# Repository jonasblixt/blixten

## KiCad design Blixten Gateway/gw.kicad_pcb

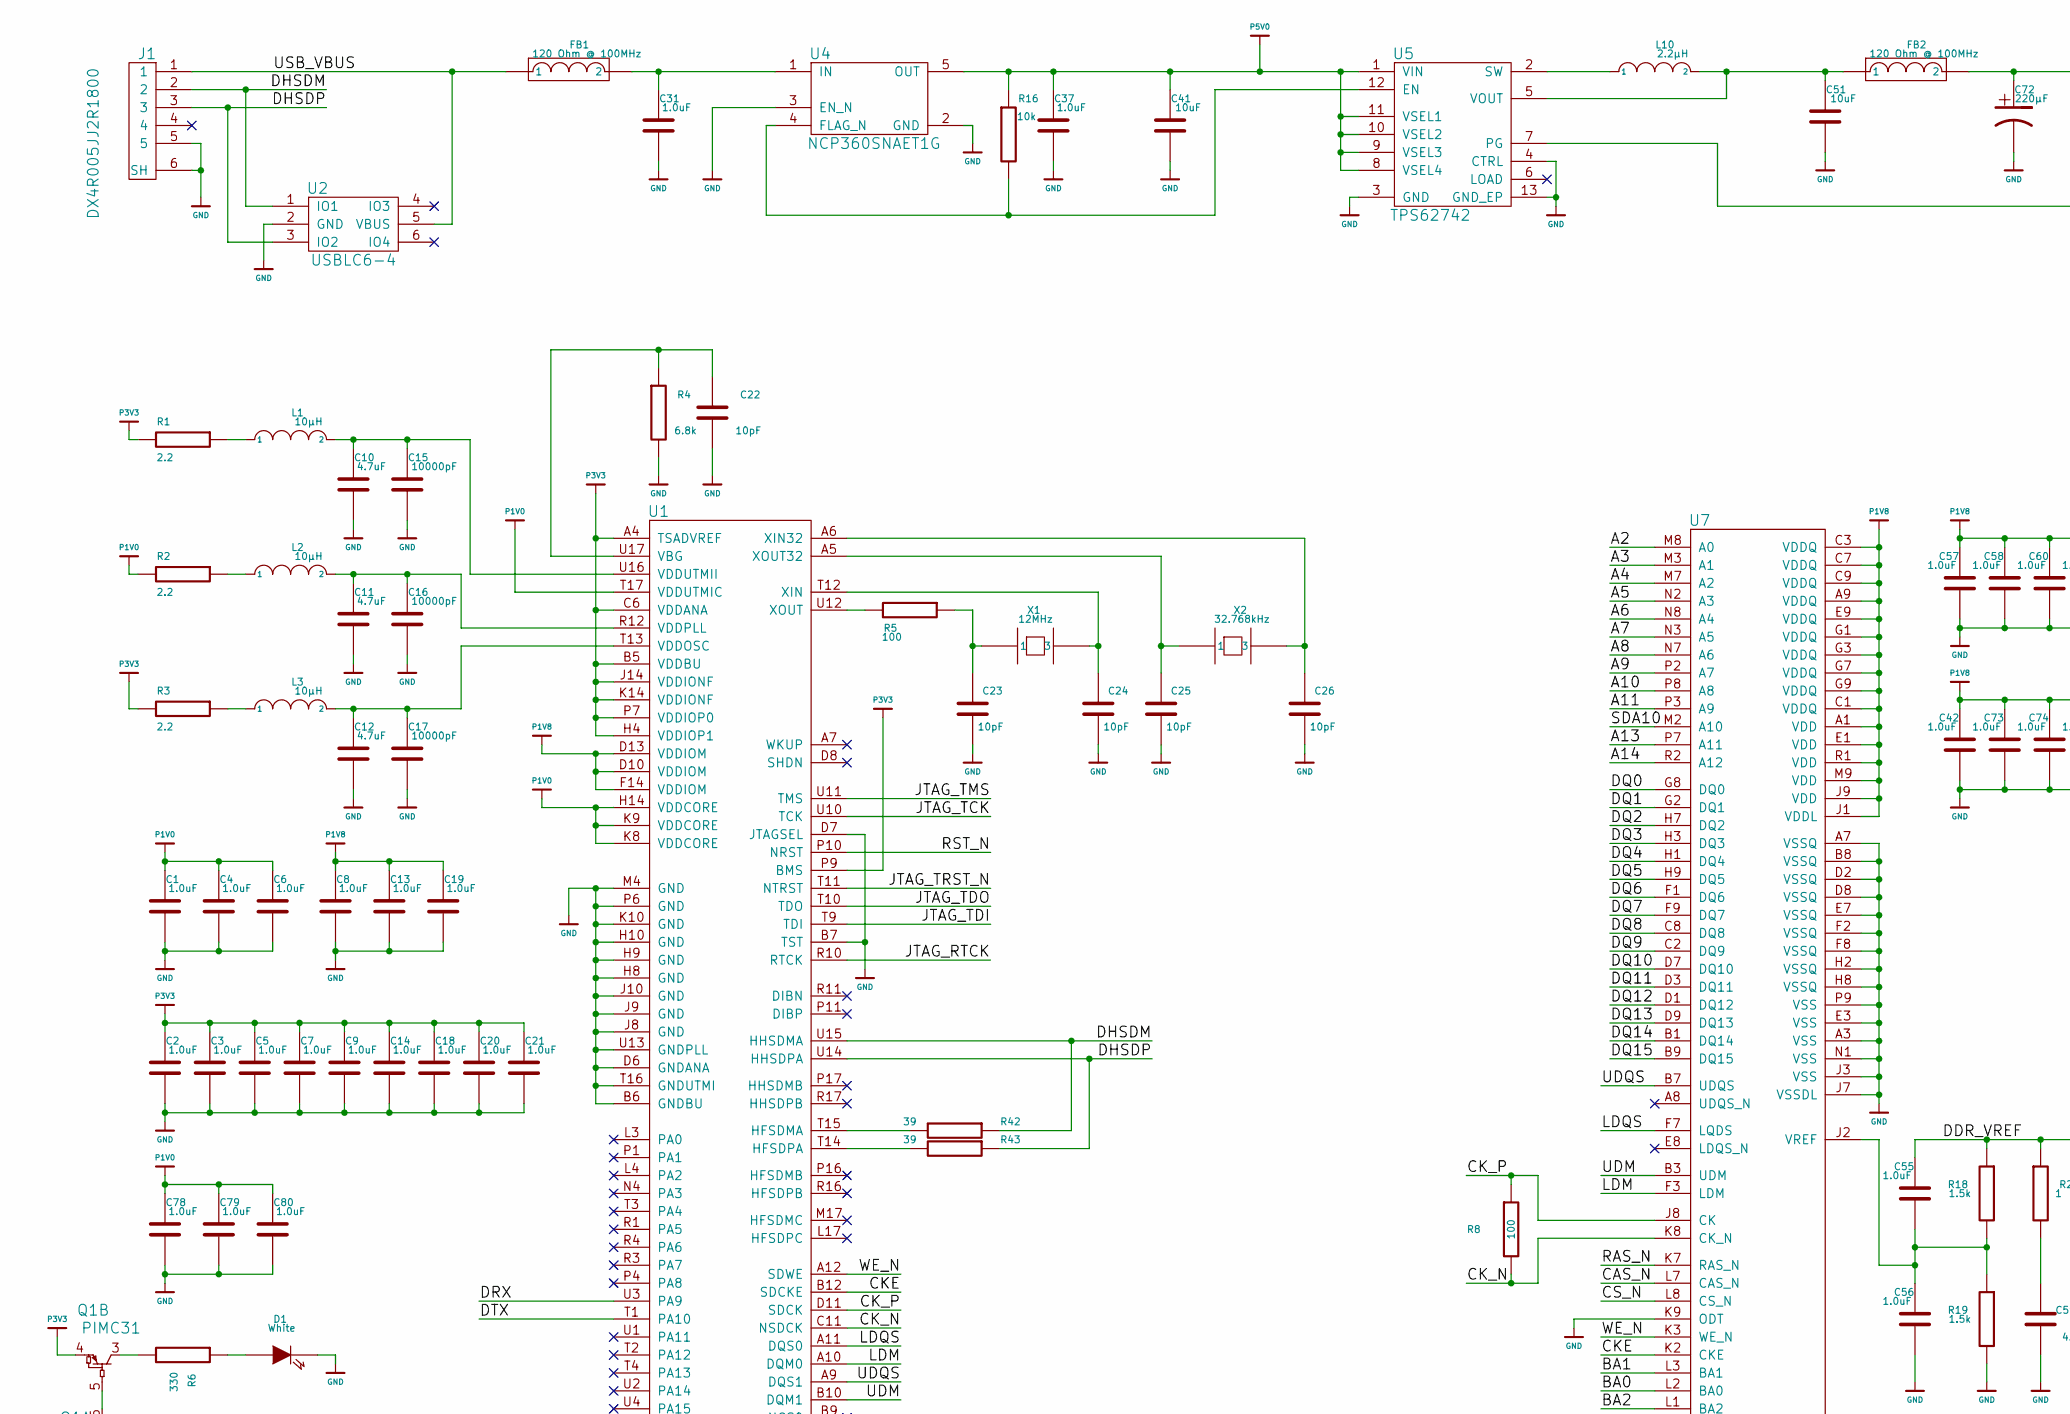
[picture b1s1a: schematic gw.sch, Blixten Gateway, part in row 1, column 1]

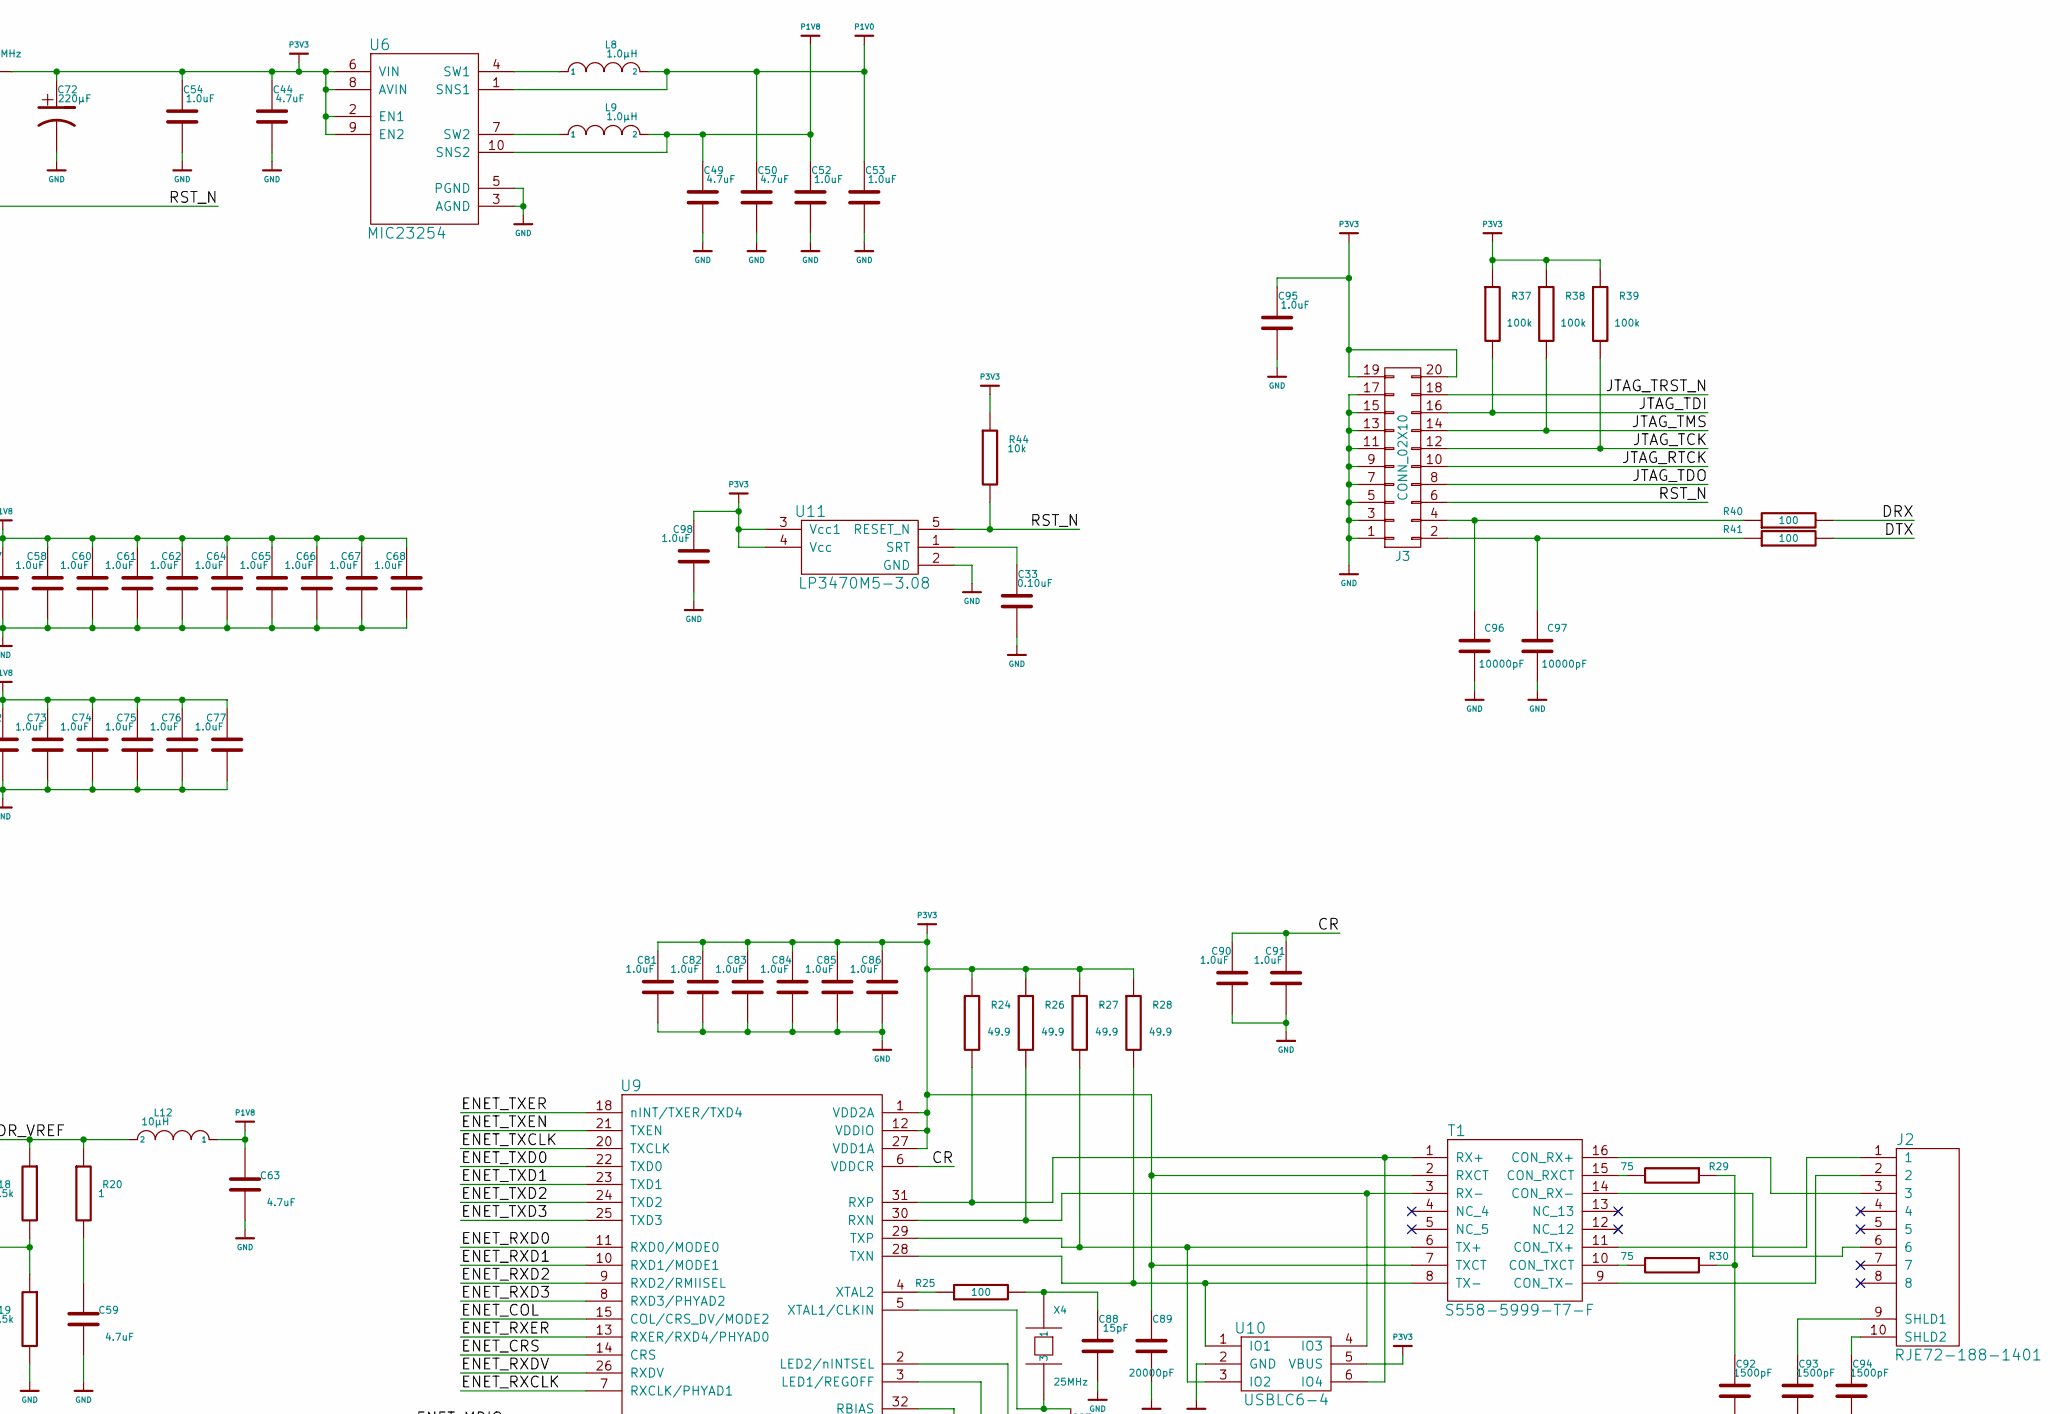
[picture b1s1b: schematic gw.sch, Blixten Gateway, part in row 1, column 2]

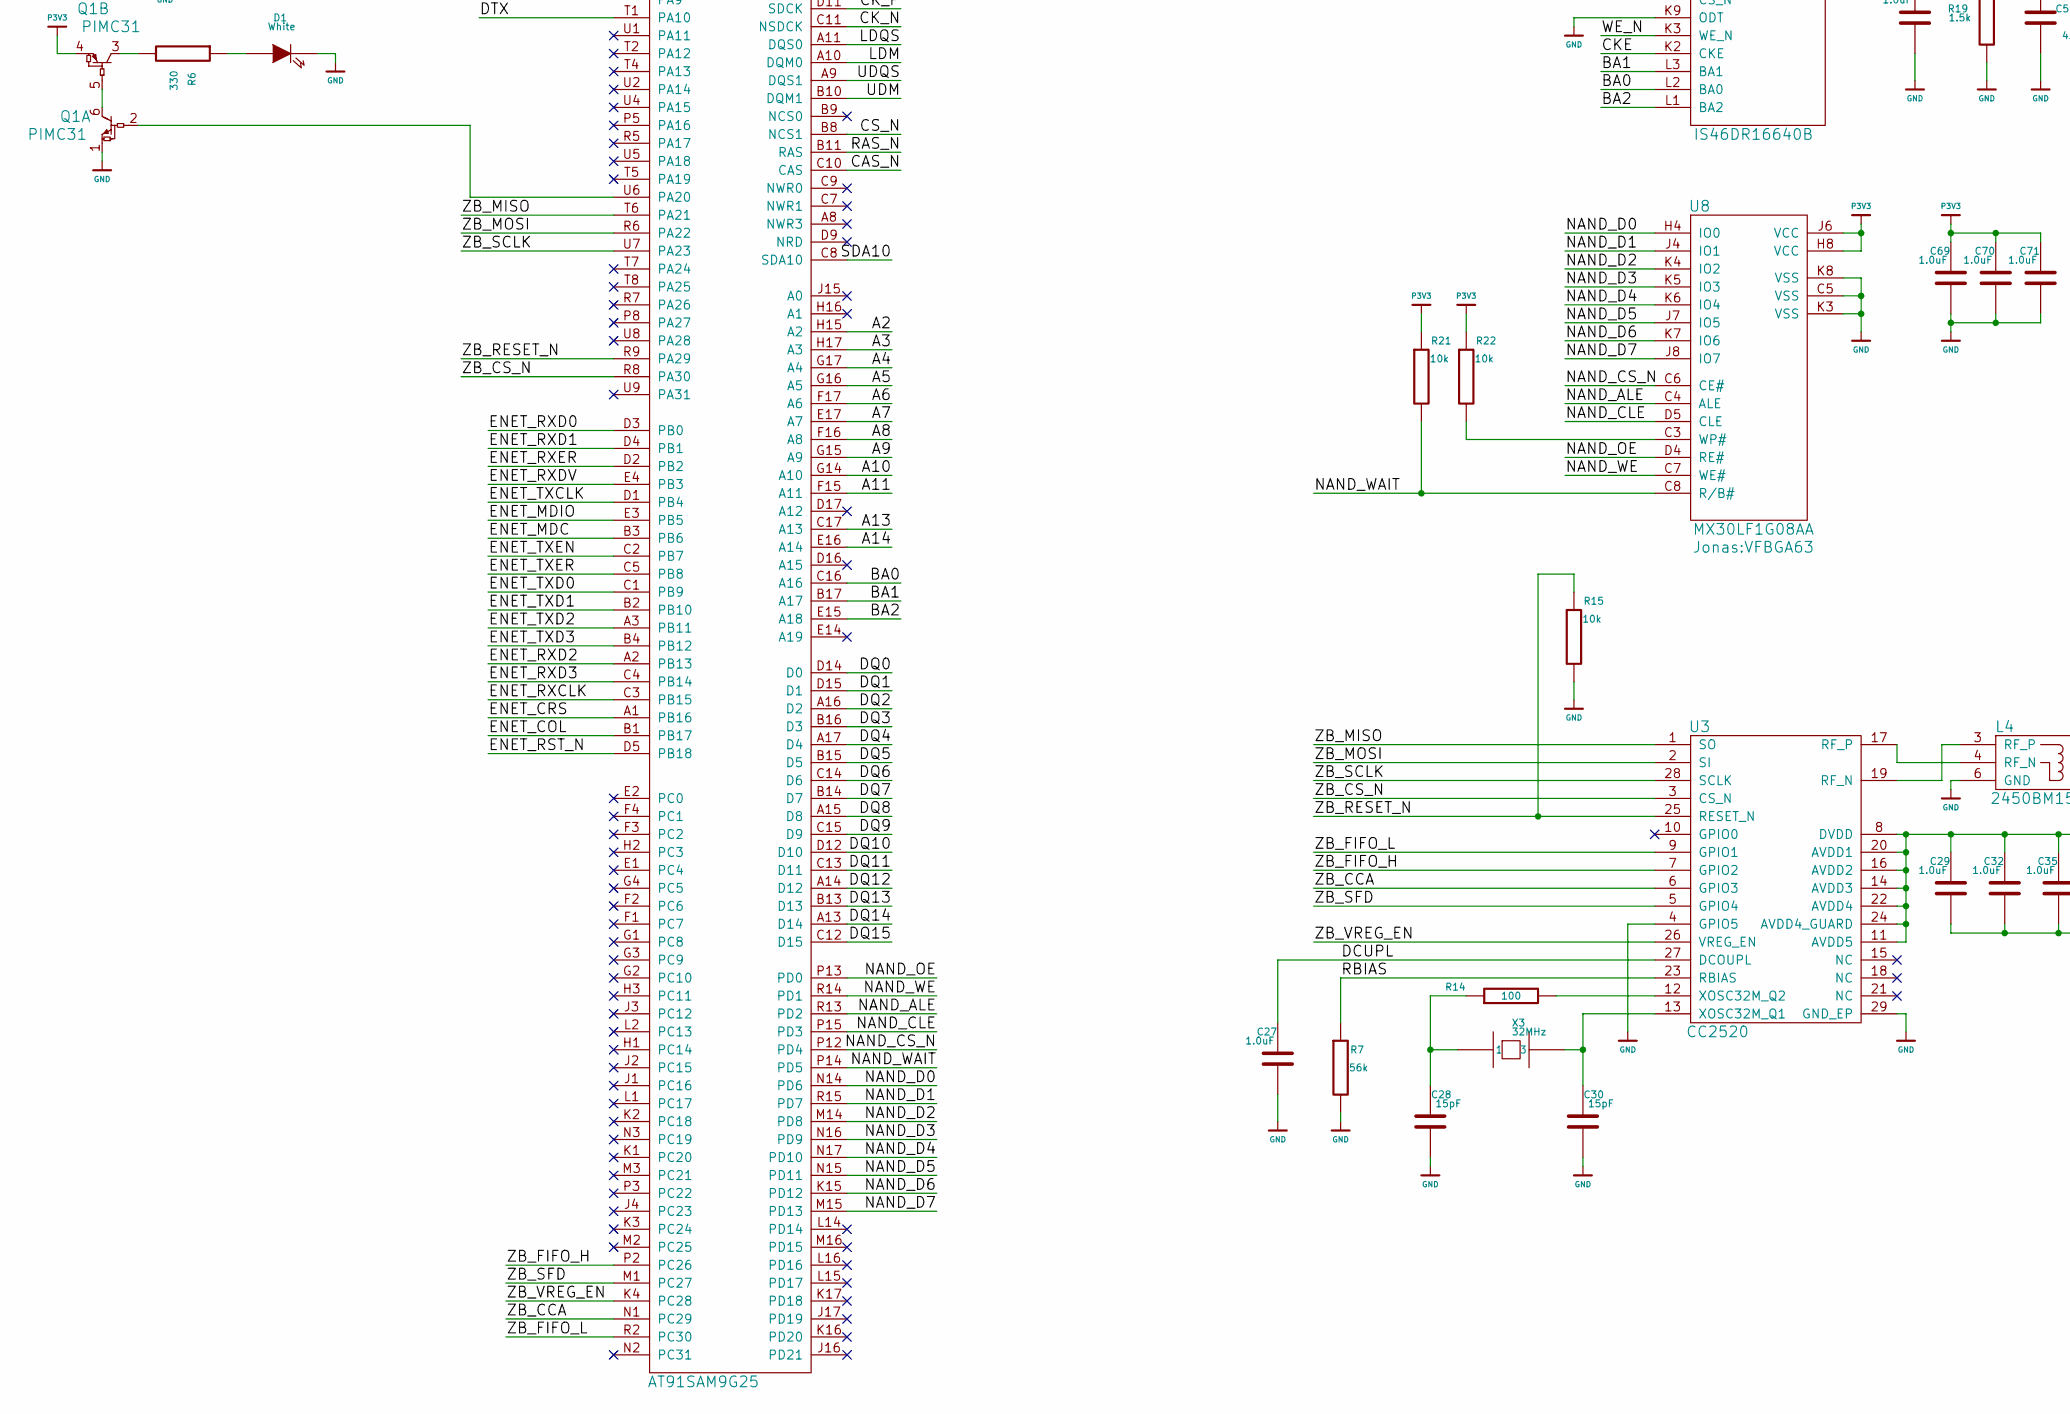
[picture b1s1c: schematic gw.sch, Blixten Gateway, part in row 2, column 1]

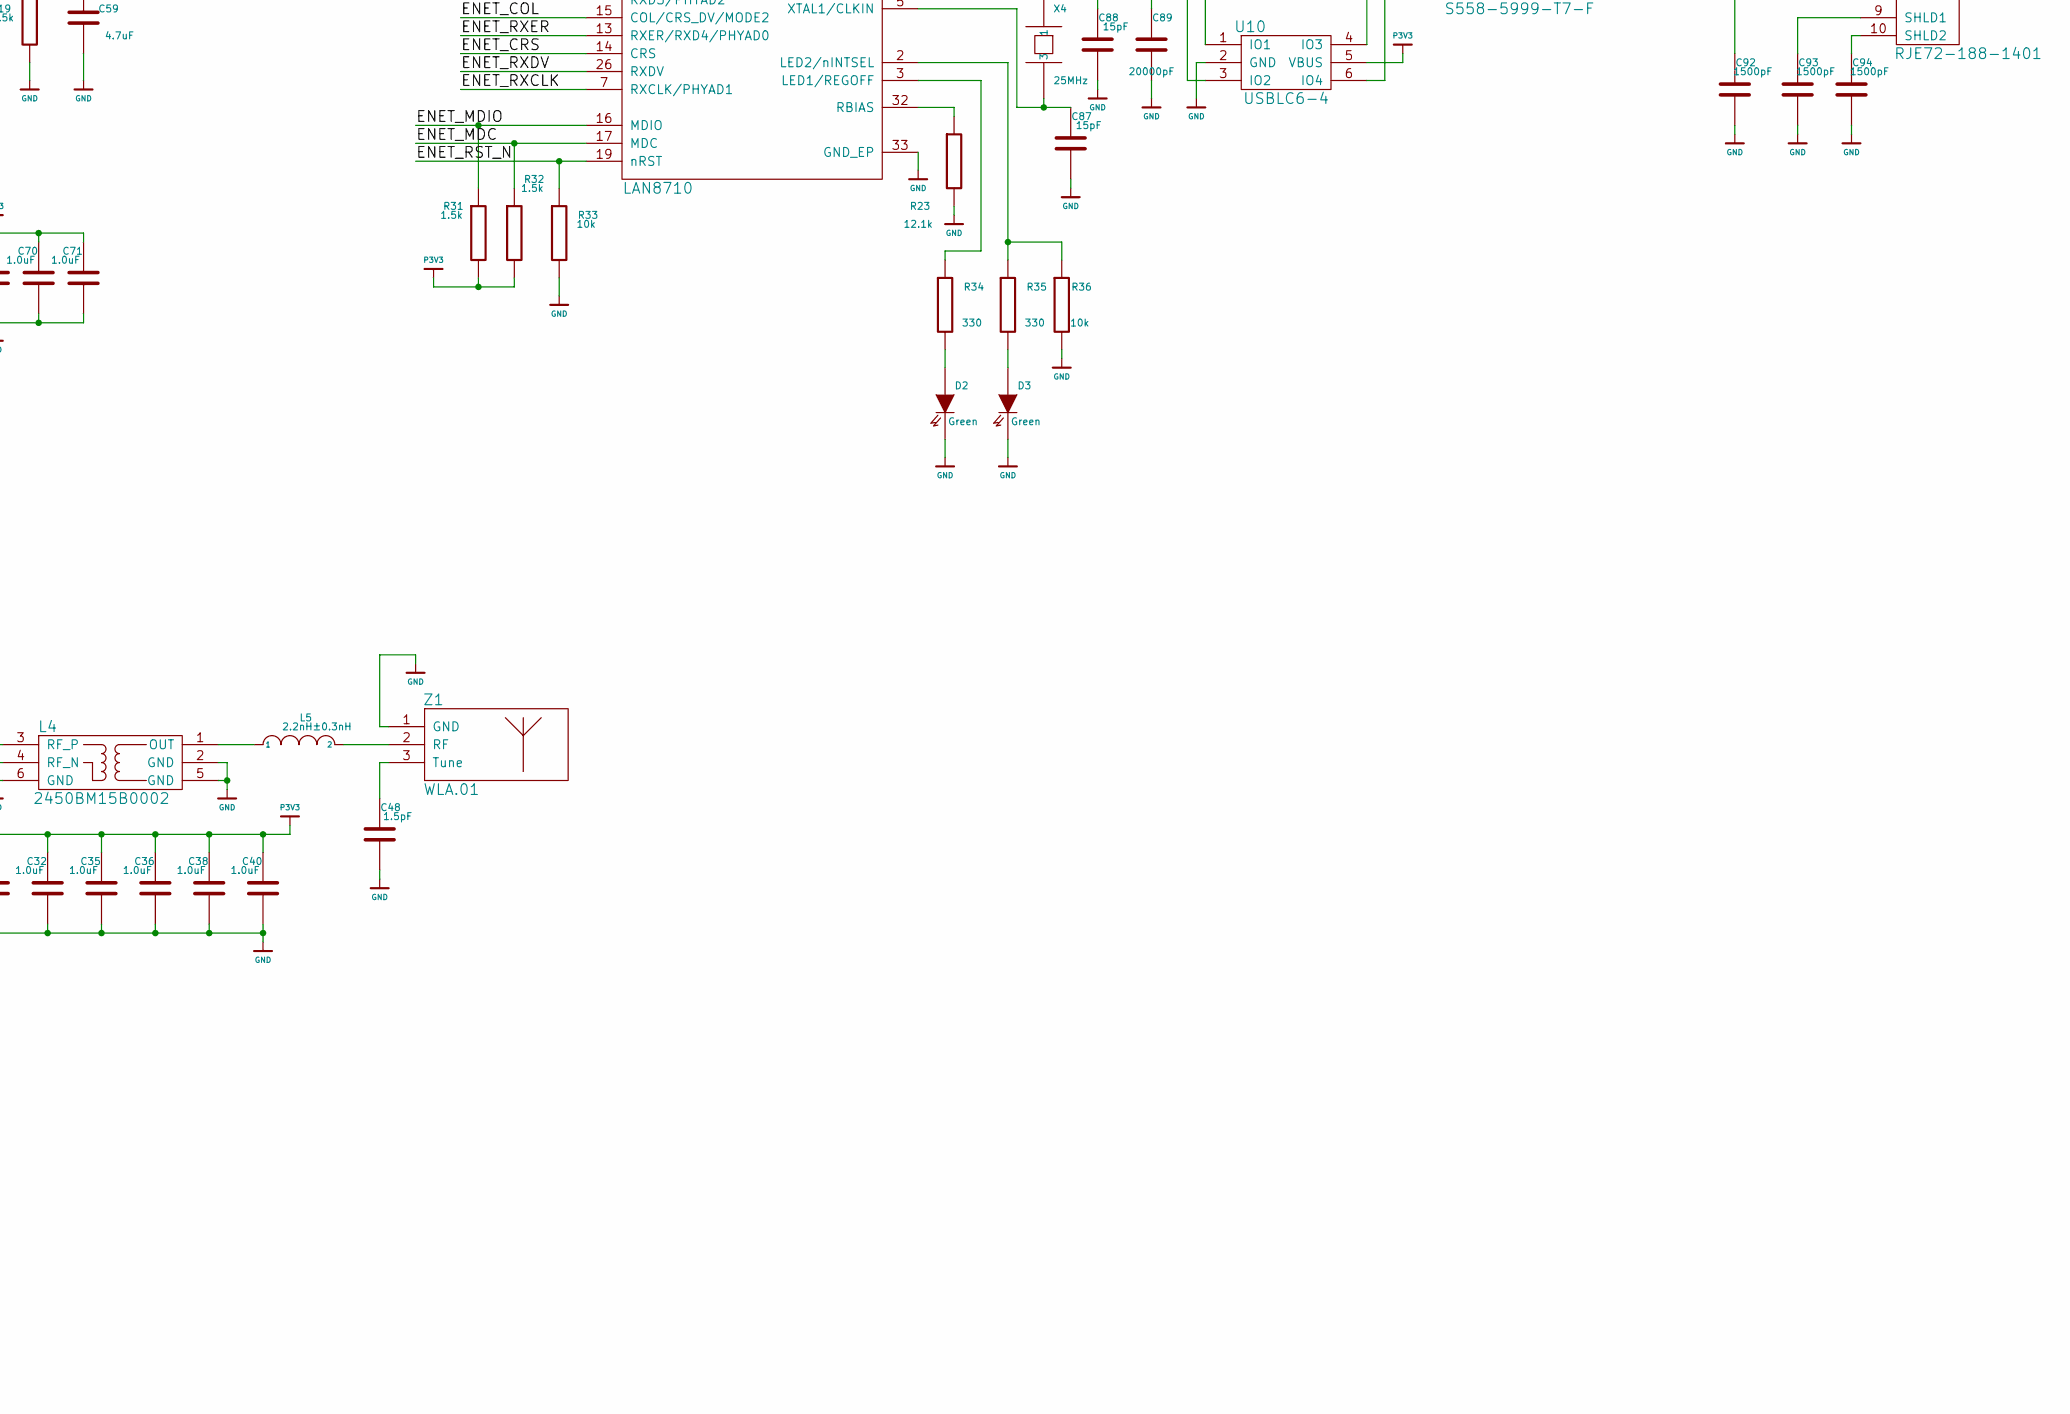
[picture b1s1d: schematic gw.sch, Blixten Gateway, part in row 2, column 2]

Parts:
C1, C2, C3, C4, C5, C6, C7, C8, C9, C13, C14, C18, C19, C20, C21, C27, C29, C32, C35, C36, C38, C40, C42, C52, C53, C55, C56, C57, C58, C60, C61, C62, C64, C65, C66, C67, C68, C69, C70, C71, C73, C74, C75, C76, C77, C78, C79, C80, C81, C82, C83, C84, C85, C86, C90, C91, C95, C98: C0402_1u_10Vdc_X5R; C_0402; Part Number GRM153R61A105ME95
C10, C11, C12, C44, C49, C50, C59, C63: C0603_4u7_6.3Vdc_X5R; C_0603; Part Number GRM185R60J475ME15
C15, C16, C17: C0402_10n_10Vdc_X5R; C_0402; Part Number GRM155R61A103KA01
C22, C23, C24, C25, C26: C0402_10p_100Vdc_C0G; C_0402; Part Number GRM1555C2A100GA01
C28, C30, C87, C88: C0402_15p_100Vdc_C0G; C_0402; Part Number GRM1555C2A150GA01
C31, C37, C54: C0603_1u_25Vdc_X7R; C_0603; Part Number GRM188R71E105KA12
C33: C0402_100n_100Vdc_X5R; C_0402; Part Number GRM155R62A104KE14
C41, C51: C0805_10u_25Vdc_X7R; C_0805; Part Number GRM21BZ71E106KE15
C48: C0402_1p5_100Vdc_C0G; C_0402; Part Number GRM1555C2A1R5BA01
C72: PCAP_220u_11; c_elec_5x5.3; Part Number PCG0G221MCO1GS
C89: C0805_20n_50Vdc_X7R; C_0805; Part Number GRM21BR71H203JA01
C92, C93, C94: C1206_1n5_1000Vdc_X7R; C_1206; Part Number GRM31BR73A152KW01
C96, C97: C0402_10n_50Vdc_X7R; C_0402; Part Number GRM155R71H103KA88
D1: LED0402_SMLP13WBC8W1; LED_0603; Part Number SMLP13WBC8W1
D2, D3: LED0402_SML-P11MTT86; LED_0603; Part Number SML-P11MTT86
FB1, FB2: BL0603_BLM18KG121TN1D; R_0603; Part Number BLM18KG121TN1D
J1: DX4R005JJ2R1800; USB_Micro-B
J2: RJE72-188-1401
J3: CONN_02X10; TFM-110-02-S-D-WT
L1, L2, L3: LQM21FN100N00L; R_0805; Part Number LQM21FN100N00L
L4: 2450BM15B0002
L5: LQG15HN_2n2; R_0402; Part Number LQG15HN2N2S02p
L8, L9: LQM21PN1R0MC0D; R_0805; Part Number LQM21PN1R0MC0D
L10: IHLP1212_2u2_2; IHLP1212; Part Number IHLP1212BZER2R2M11
L12: LQH2MCN100K02L; R_0805; Part Number LQH2MCN100K02L
Q1: PIMC31; SOT-23-6
R1, R2, R3: R0402_2R20; R_0402; Part Number CRCW04022R20FKED
R4: R0402_6k80; R_0402; Part Number CRCW04026K80FKED
R5, R8, R14, R25, R40, R41: R0402_100R; R_0402; Part Number CRCW0402100RFKED
R6, R34, R35: R0402_330R; R_0402; Part Number CRCW0402330RFKED
R7: R0402_56k; R_0402; Part Number CRCW040256K0FKED
R15, R16, R21, R22, R33, R36, R44: R0402_10k; R_0402; Part Number CRCW040210K0FKED
R18, R19, R31, R32: R0402_1k50; R_0402; Part Number CRCW04021K50FKED
R20: R0402_1R; R_0402; Part Number CRCW04021R00FKED
R23: R0402_12k10; R_0402; Part Number CRCW040212K1FKED
R24, R26, R27, R28: R0603_49R90; R_0603; Part Number CRCW060349R9FKEA
R29, R30: R0603_75R; R_0603; Part Number CRCW060375R0FKEA
R37, R38, R39: R0402_100k; R_0402; Part Number CRCW0402100KFKED
R42, R43: R0402_39R; R_0402; Part Number CRCW040239R0FKED
T1: S558-5999-T7-F; SO-16-W
U1: AT91SAM9G25; 217LFBGA
U2, U10: USBLC6-4; SOT-23-6
U3: CC2520; QFN-28-1EP_5x5mm_Pitch0.5mm
U4: NCP360SNAET1G; SOT-23-5
U5: TPS62742; R-PWSON-N12
U6: MIC23254; MLF-10
U7: IS46DR16640B; BGA-90-0.8mm
U8: MX30LF1G08AA; VFBGA63
U9: LAN8710; QFN-32-1EP_5x5mm_Pitch0.5mm
U11: LP3470M5-3.08; SOT-23-5
X1: NX3225GA-12.000M-STD-CRA-1; NX3225; Part Number NX3225GA-12.000M-STD-CRA-1
X2: NX2012SA-32.768K-STD-MUB-1; NX2012; Part Number NX2012SA-32.768K-STD-MUB-1
X3: NX2520SA-32.000000MHZ; NX2520; Part Number NX2520SA-32.000000MHZ
X4: NX2520SA-25.000M-STD-CSW-5; NX2520; Part Number NX2520SA-25.000M-STD-CSW-5
Z1: WLA.01

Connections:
/A2: U1.H15 (A2), U7.M8 (A0)
/A3: U1.H17 (A3), U7.M3 (A1)
/A4: U1.G17 (A4), U7.M7 (A2)
/A5: U1.G16 (A5), U7.N2 (A3)
/A6: U1.F17 (A6), U7.N8 (A4)
/A7: U1.E17 (A7), U7.N3 (A5)
/A8: U1.F16 (A8), U7.N7 (A6)
/A9: U1.G15 (A9), U7.P2 (A7)
/A10: U1.G14 (A10), U7.P8 (A8)
/A11: U1.F15 (A11), U7.P3 (A9)
/A13: U1.C17 (A13), U7.P7 (A11)
/A14: U1.E16 (A14), U7.R2 (A12)
/BA0: U1.C16 (A16), U7.L2 (BA0)
/BA1: U1.B17 (A17), U7.L3 (BA1)
/BA2: U1.E15 (A18), U7.L1 (BA2)
/CAS_N: U1.C10 (CAS), U7.L7 (CAS_N)
/CKE: U1.B12 (SDCKE), U7.K2 (CKE)
/CK_N: R8.2, U1.C11 (NSDCK), U7.K8 (CK_N)
/CK_P: R8.1, U1.D11 (SDCK), U7.J8 (CK)
/CR: C90.1, C91.1, U9.6 (VDDCR)
/CS_N: U1.B8 (NCS1), U7.L8 (CS_N)
/DCUPL: C27.1, U3.27 (DCOUPL)
/DDR_VREF: C55.1, L12.2, R18.1, R20.1
/DHSDM: J1.2, R42.1, U1.U15 (HHSDMA), U2.1 (IO1)
/DHSDP: J1.3, R43.1, U1.U14 (HHSDPA), U2.3 (IO2)
/DQ0: U1.D14 (D0), U7.G8 (DQ0)
/DQ1: U1.D15 (D1), U7.G2 (DQ1)
/DQ2: U1.A16 (D2), U7.H7 (DQ2)
/DQ3: U1.B16 (D3), U7.H3 (DQ3)
/DQ4: U1.A17 (D4), U7.H1 (DQ4)
/DQ5: U1.B15 (D5), U7.H9 (DQ5)
/DQ6: U1.C14 (D6), U7.F1 (DQ6)
/DQ7: U1.B14 (D7), U7.F9 (DQ7)
/DQ8: U1.A15 (D8), U7.C8 (DQ8)
/DQ9: U1.C15 (D9), U7.C2 (DQ9)
/DQ10: U1.D12 (D10), U7.D7 (DQ10)
/DQ11: U1.C13 (D11), U7.D3 (DQ11)
/DQ12: U1.A14 (D12), U7.D1 (DQ12)
/DQ13: U1.B13 (D13), U7.D9 (DQ13)
/DQ14: U1.A13 (D14), U7.B1 (DQ14)
/DQ15: U1.C12 (D15), U7.B9 (DQ15)
/DRX: R40.2, U1.U3 (PA9)
/DTX: R41.2, U1.T1 (PA10)
/ENET_COL: U1.B1 (PB17), U9.15 (COL/CRS_DV/MODE2)
/ENET_CRS: U1.A1 (PB16), U9.14 (CRS)
/ENET_MDC: R32.1, U1.B3 (PB6), U9.17 (MDC)
/ENET_MDIO: R31.1, U1.E3 (PB5), U9.16 (MDIO)
/ENET_RST_N: R33.1, U1.D5 (PB18), U9.19 (nRST)
/ENET_RXCLK: U1.C3 (PB15), U9.7 (RXCLK/PHYAD1)
/ENET_RXD0: U1.D3 (PB0), U9.11 (RXD0/MODE0)
/ENET_RXD1: U1.D4 (PB1), U9.10 (RXD1/MODE1)
/ENET_RXD2: U1.A2 (PB13), U9.9 (RXD2/RMIISEL)
/ENET_RXD3: U1.C4 (PB14), U9.8 (RXD3/PHYAD2)
/ENET_RXDV: U1.E4 (PB3), U9.26 (RXDV)
/ENET_RXER: U1.D2 (PB2), U9.13 (RXER/RXD4/PHYAD0)
/ENET_TXCLK: U1.D1 (PB4), U9.20 (TXCLK)
/ENET_TXD0: U1.C1 (PB9), U9.22 (TXD0)
/ENET_TXD1: U1.B2 (PB10), U9.23 (TXD1)
/ENET_TXD2: U1.A3 (PB11), U9.24 (TXD2)
/ENET_TXD3: U1.B4 (PB12), U9.25 (TXD3)
/ENET_TXEN: U1.C2 (PB7), U9.21 (TXEN)
/ENET_TXER: U1.C5 (PB8), U9.18 (nINT/TXER/TXD4)
/JTAG_RTCK: J3.10, U1.R10 (RTCK)
/JTAG_TCK: J3.12, R39.2, U1.U10 (TCK)
/JTAG_TDI: J3.16, R37.2, U1.T9 (TDI)
/JTAG_TDO: J3.8, U1.T10 (TDO)
/JTAG_TMS: J3.14, R38.2, U1.U11 (TMS)
/JTAG_TRST_N: J3.18, U1.T11 (NTRST)
/LDM: U1.A10 (DQM0), U7.F3 (LDM)
/LDQS: U1.A11 (DQS0), U7.F7 (LQDS)
/NAND_ALE: U1.R13 (PD2), U8.C4 (ALE)
/NAND_CLE: U1.P15 (PD3), U8.D5 (CLE)
/NAND_CS_N: U1.P12 (PD4), U8.C6 (CE#)
/NAND_D0: U1.N14 (PD6), U8.H4 (IO0)
/NAND_D1: U1.R15 (PD7), U8.J4 (IO1)
/NAND_D2: U1.M14 (PD8), U8.K4 (IO2)
/NAND_D3: U1.N16 (PD9), U8.K5 (IO3)
/NAND_D4: U1.N17 (PD10), U8.K6 (IO4)
/NAND_D5: U1.N15 (PD11), U8.J7 (IO5)
/NAND_D6: U1.K15 (PD12), U8.K7 (IO6)
/NAND_D7: U1.M15 (PD13), U8.J8 (IO7)
/NAND_OE: U1.P13 (PD0), U8.D4 (RE#)
/NAND_WAIT: R21.2, U1.P14 (PD5), U8.C8 (R/B#)
/NAND_WE: U1.R14 (PD1), U8.C7 (WE#)
/RAS_N: U1.B11 (RAS), U7.K7 (RAS_N)
/RBIAS: R7.1, U3.23 (RBIAS)
/RST_N: J3.6, R44.2, U1.P10 (NRST), U5.7 (PG), U11.5 (RESET_N)
/SDA10: U1.C8 (SDA10), U7.M2 (A10)
/UDM: U1.B10 (DQM1), U7.B3 (UDM)
/UDQS: U1.A9 (DQS1), U7.B7 (UDQS)
/USB_VBUS: FB1.1, J1.1, U2.5 (VBUS)
/WE_N: U1.A12 (SDWE), U7.K3 (WE_N)
/ZB_CCA: U1.N1 (PC29), U3.6 (GPIO3)
/ZB_CS_N: U1.R8 (PA30), U3.3 (CS_N)
/ZB_FIFO_H: U1.P2 (PC26), U3.7 (GPIO2)
/ZB_FIFO_L: U1.R2 (PC30), U3.9 (GPIO1)
/ZB_MISO: U1.T6 (PA21), U3.1 (SO)
/ZB_MOSI: U1.R6 (PA22), U3.2 (SI)
/ZB_RESET_N: R15.1, U1.R9 (PA29), U3.25 (RESET_N)
/ZB_SCLK: U1.U7 (PA23), U3.28 (SCLK)
/ZB_SFD: U1.M1 (PC27), U3.5 (GPIO4)
/ZB_VREG_EN: U1.K4 (PC28), U3.26 (VREG_EN)
GND: C1.2, C2.2, C3.2, C4.2, C5.2, C6.2, C7.2, C8.2, C9.2, C10.2, C11.2, C12.2, C13.2, C14.2, C15.2, C16.2, C17.2, C18.2, C19.2, C20.2, C21.2, C22.2, C23.2, C24.2, C25.2, C26.2, C27.2, C28.2, C29.2, C30.2, C31.2, C32.2, C33.2, C35.2, C36.2, C37.2, C38.2, C40.2, C41.2, C42.2, C44.2, C48.2, C49.2, C50.2, C51.2, C52.2, C53.2, C54.2, C56.2, C57.2, C58.2, C59.2, C60.2, C61.2, C62.2, C63.2, C64.2, C65.2, C66.2, C67.2, C68.2, C69.2, C70.2, C71.2, C72.2, C73.2, C74.2, C75.2, C76.2, C77.2, C78.2, C79.2, C80.2, C81.2, C82.2, C83.2, C84.2, C85.2, C86.2, C87.2, C88.2, C89.2, C90.2, C91.2, C92.2, C93.2, C94.2, C95.2, C96.2, C97.2, C98.2, D1.2, D2.2, D3.2, J1.5, J1.6 (SH), J3.1, J3.3, J3.5, J3.7, J3.9, J3.11, J3.13, J3.15, J3.17, L4.2 (GND), L4.5 (GND), L4.6 (GND), Q1.1, R4.2, R7.2, R15.2, R19.2, R23.2, R33.2, R36.2, U1.B6 (GNDBU), U1.B7 (TST), U1.D6 (GNDANA), U1.D7 (JTAGSEL), U1.H8 (GND), U1.H9 (GND), U1.H10 (GND), U1.J8 (GND), U1.J9 (GND), U1.J10 (GND), U1.K10 (GND), U1.M4 (GND), U1.P6 (GND), U1.T16 (GNDUTMI), U1.U13 (GNDPLL), U2.2 (GND), U3.4 (GPIO5), U3.29 (GND_EP), U4.2 (GND), U4.3 (EN_N), U5.3 (GND), U5.4 (CTRL), U5.13 (GND_EP), U6.3 (AGND), U6.5 (PGND), U7.A3 (VSS), U7.A7 (VSSQ), U7.B8 (VSSQ), U7.D2 (VSSQ), U7.D8 (VSSQ), U7.E3 (VSS), U7.E7 (VSSQ), U7.F2 (VSSQ), U7.F8 (VSSQ), U7.H2 (VSSQ), U7.H8 (VSSQ), U7.J3 (VSS), U7.J7 (VSSDL), U7.K9 (ODT), U7.N1 (VSS), U7.P9 (VSS), U8.C5 (VSS), U8.K3 (VSS), U8.K8 (VSS), U9.33 (GND_EP), U10.2 (GND), U11.2 (GND), Z1.1 (GND)
unnamed: C10.1, C15.1, L1.2, U1.U16 (VDDUTMII)
unnamed: C11.1, C16.1, L2.2, U1.R12 (VDDPLL)
unnamed: C12.1, C17.1, L3.2, U1.T13 (VDDOSC)
unnamed: C22.1, R4.1, U1.U17 (VBG)
unnamed: C23.1, R5.1, X1.1
unnamed: C24.1, U1.T12 (XIN), X1.3
unnamed: C25.1, U1.A5 (XOUT32), X2.1
unnamed: C26.1, U1.A6 (XIN32), X2.3
unnamed: C28.1, R14.1, X3.1
unnamed: C30.1, U3.13 (XOSC32M_Q1), X3.3
unnamed: C31.1, FB1.2, U4.1 (IN)
unnamed: C33.1, U11.1 (SRT)
unnamed: C48.1, Z1.3 (Tune)
unnamed: C51.1, FB2.1, L10.2, U5.5 (VOUT)
unnamed: C55.2, C56.1, R18.2, R19.1, U7.J2 (VREF)
unnamed: C59.1, R20.2
unnamed: C87.1, U9.5 (XTAL1/CLKIN), X4.3
unnamed: C88.1, R25.2, X4.1
unnamed: C92.1, R29.1, R30.1
unnamed: C93.1, J2.9 (SHLD1)
unnamed: C94.1, J2.10 (SHLD2)
unnamed: C96.1, J3.4, R40.1
unnamed: C97.1, J3.2, R41.1
unnamed: D1.1, R6.1
unnamed: D2.1, R34.2
unnamed: D3.1, R35.2
unnamed: J2.1, T1.11 (CON_TX+)
unnamed: J2.2, T1.9 (CON_TX-)
unnamed: J2.3, T1.16 (CON_RX+)
unnamed: J2.6, T1.14 (CON_RX-)
unnamed: L1.1, R1.1
unnamed: L2.1, R2.1
unnamed: L3.1, R3.1
unnamed: L4.1 (OUT), L5.1
unnamed: L4.3 (RF_P), U3.19 (RF_N)
unnamed: L4.4 (RF_N), U3.17 (RF_P)
unnamed: L5.2, Z1.2 (RF)
unnamed: L8.1, U6.4 (SW1)
unnamed: L9.1, U6.7 (SW2)
unnamed: L10.1, U5.2 (SW)
unnamed: Q1.2, U1.U6 (PA20)
unnamed: Q1.3, R6.2
unnamed: Q1.5, Q1.6
unnamed: R5.2, U1.U12 (XOUT)
unnamed: R14.2, U3.12 (XOSC32M_Q2)
unnamed: R16.2, U4.4 (FLAG_N), U5.12 (EN)
unnamed: R22.2, U8.C3 (WP#)
unnamed: R23.1, U9.32 (RBIAS)
unnamed: R24.2, T1.1 (RX+), U9.31 (RXP), U10.6 (IO4)
unnamed: R25.1, U9.4 (XTAL2)
unnamed: R26.2, T1.3 (RX-), U9.30 (RXN), U10.4 (IO3)
unnamed: R27.2, T1.6 (TX+), U9.29 (TXP), U10.3 (IO2)
unnamed: R28.2, T1.8 (TX-), U9.28 (TXN), U10.1 (IO1)
unnamed: R29.2, T1.15 (CON_RXCT)
unnamed: R30.2, T1.10 (CON_TXCT)
unnamed: R34.1, U9.3 (LED1/REGOFF)
unnamed: R35.1, R36.1, U9.2 (LED2/nINTSEL)
unnamed: R42.2, U1.T15 (HFSDMA)
unnamed: R43.2, U1.T14 (HFSDPA)
P1V0: C1.1, C4.1, C6.1, C50.1, C53.1, C78.1, C79.1, C80.1, L8.2, R2.2, U1.H14 (VDDCORE), U1.K8 (VDDCORE), U1.K9 (VDDCORE), U1.T17 (VDDUTMIC), U6.1 (SNS1)
P1V8: C8.1, C13.1, C19.1, C42.1, C49.1, C52.1, C57.1, C58.1, C60.1, C61.1, C62.1, C63.1, C64.1, C65.1, C66.1, C67.1, C68.1, C73.1, C74.1, C75.1, C76.1, C77.1, L9.2, L12.1, U1.D10 (VDDIOM), U1.D13 (VDDIOM), U1.F14 (VDDIOM), U6.10 (SNS2), U7.A1 (VDD), U7.A9 (VDDQ), U7.C1 (VDDQ), U7.C3 (VDDQ), U7.C7 (VDDQ), U7.C9 (VDDQ), U7.E1 (VDD), U7.E9 (VDDQ), U7.G1 (VDDQ), U7.G3 (VDDQ), U7.G7 (VDDQ), U7.G9 (VDDQ), U7.J1 (VDDL), U7.J9 (VDD), U7.M9 (VDD), U7.R1 (VDD)
P3V3: C2.1, C3.1, C5.1, C7.1, C9.1, C14.1, C18.1, C20.1, C21.1, C29.1, C32.1, C35.1, C36.1, C38.1, C40.1, C44.1, C54.1, C69.1, C70.1, C71.1, C72.1, C81.1, C82.1, C83.1, C84.1, C85.1, C86.1, C89.1, C95.1, C98.1, FB2.2, J3.19, J3.20, Q1.4, R1.2, R3.2, R21.1, R22.1, R24.1, R26.1, R27.1, R28.1, R31.2, R32.2, R37.1, R38.1, R39.1, R44.1, T1.2 (RXCT), T1.7 (TXCT), U1.A4 (TSADVREF), U1.B5 (VDDBU), U1.C6 (VDDANA), U1.H4 (VDDIOP1), U1.J14 (VDDIONF), U1.K14 (VDDIONF), U1.P7 (VDDIOP0), U1.P9 (BMS), U3.8 (DVDD), U3.11 (AVDD5), U3.14 (AVDD3), U3.16 (AVDD2), U3.20 (AVDD1), U3.22 (AVDD4), U3.24 (AVDD4_GUARD), U6.2 (EN1), U6.6 (VIN), U6.8 (AVIN), U6.9 (EN2), U8.H8 (VCC), U8.J6 (VCC), U9.1 (VDD2A), U9.12 (VDDIO), U9.27 (VDD1A), U10.5 (VBUS), U11.3 (Vcc1), U11.4 (Vcc)
P5V0: C37.1, C41.1, R16.1, U4.5 (OUT), U5.1 (VIN), U5.8 (VSEL4), U5.9 (VSEL3), U5.10 (VSEL2), U5.11 (VSEL1)

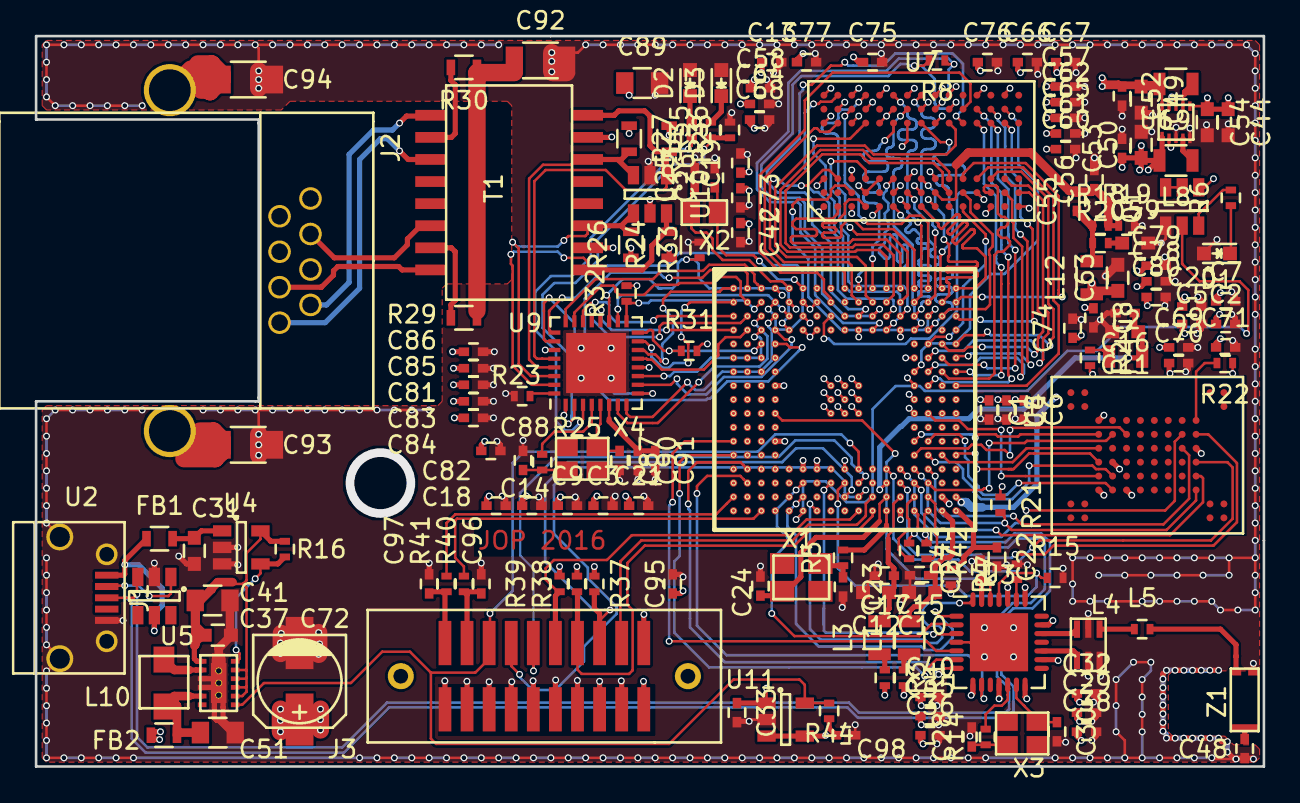
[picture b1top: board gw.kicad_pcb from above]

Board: 4 copper layers, 70.6 x 42.0 mm, 165 parts (0 on the bottom side), 166 nets.

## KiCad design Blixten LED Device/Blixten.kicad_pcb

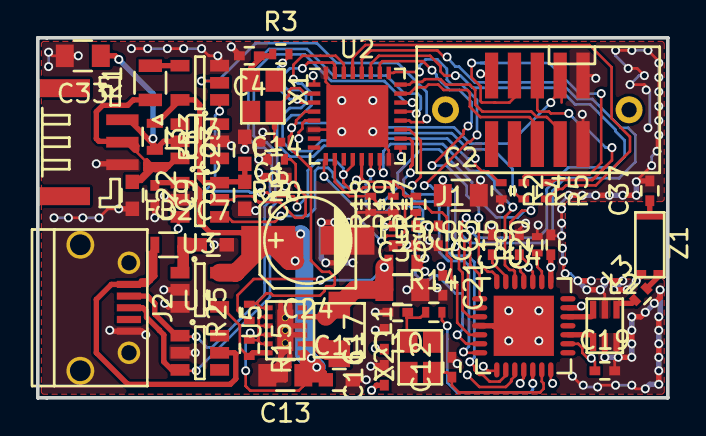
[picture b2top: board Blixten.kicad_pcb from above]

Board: 4 copper layers, 35.0 x 20.0 mm, 60 parts (0 on the bottom side), 49 nets.

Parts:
C1, C4, C10, C12: C0402_15p_100Vdc_C0G; C_0402
C2, C13, C30, C33: C0805_10u_25Vdc_X7R; C_0805
C3, C5, C6, C8, C9, C14, C15, C16, C17, C19, C20, C21: C0402_1u_10Vdc_X5R; C_0402
C7, C11, C18, C23: C0603_1u_25Vdc_X7R; C_0603
C22: C0603_10n_100Vdc_X7R; C_0603
C24: PCAP_100u_16; c_elec_5x5.3
C37: C0402_1p5_100Vdc_C0G; C_0402
FB2, FB3, FB5: BL0603_BLM18KG121TN1D; R_0603
J1: TFM-105-02-S-D-WT
J2: DX4R005JJ2R1800; USB_Micro-B
J3: CONN_01X03; JST_GH_SM03B-GHS-TB_03x1.25mm_Angled
L1: IHLP1212_2u2_2; IHLP1212
L2: 2450BM15B0002
L3: LQG15HN_2n2; R_0402
R1: R0805_100R; R_0805
R2, R15, R17, R18, R19, R25: R0402_10k; R_0402
R3, R4, R5, R14: R0402_100R; R_0402
R9: R0402_56k; R_0402
R20: R0402_44k20; R_0402
U1, U8: USBLC6-4; SOT-23-6
U2: STM32F302K8U6; QFN-32-1EP_5x5mm_Pitch0.5mm
U3: NCP360SNAET1G; SOT-23-5
U4: CC2520; QFN-28-1EP_5x5mm_Pitch0.5mm
U5: TPS62742; R-PWSON-N12
U6: NCP380HSNAJAAT1G; SOT-23-6
U7: SN74LV1T126; SOT-23-5
X1: NX2520SA-16.000000MHZ; NX2520
X2: NX2520SA-32.000000MHZ; NX2520
Z1: WLA.01

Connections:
/NEOPIXEL_OUT: U2.20, U7.2
/P5V_EN: R18.2, U2.12, U6.3, U7.1
/P5V_ERR_N: R19.2, U2.13, U6.4
/RST_N: J1.8, R25.2, U2.4, U5.7
/SWCLK: J1.7, U2.24
/SWDIO: J1.5, U2.23
/USART1_RX: R4.2, U2.30
/USART1_TX: R5.2, U2.29
/USB_DN: J2.2, U1.1, U2.21
/USB_DP: J2.3, U1.3, U2.22
/USB_VBUS: FB2.1, J2.1, U1.5
/ZB_CCA: U2.14, U4.6
/ZB_CS_N: U2.25, U4.3
/ZB_DCUPL: C8.1, U4.27
/ZB_FIFO: U2.19, U4.9
/ZB_FIFOP: U2.18, U4.7
/ZB_MISO: U2.27, U4.1
/ZB_MOSI: U2.28, U4.2
/ZB_RBIAS: R9.1, U4.23
/ZB_RESET_N: R17.1, U2.10, U4.25
/ZB_SCLK: U2.26, U4.28
/ZB_SFD: U2.9, U4.5
/ZB_VREG_EN: U2.15, U4.26
GND: C1.2, C2.2, C3.2, C4.2, C5.2, C6.2, C7.2, C8.2, C9.2, C10.2, C11.2, C12.2, C13.2, C14.2, C15.2, C16.2, C17.2, C18.2, C19.2, C20.2, C21.2, C22.2, C23.2, C24.2, C30.2, C33.2, C37.2, J1.9, J1.10, J2.5, J2.6, J3.3, L2.2, L2.5, L2.6, R2.2, R9.2, R17.2, R18.1, R20.2, U1.2, U2.6, U2.16, U2.32, U2.33, U3.2, U3.3, U4.4, U4.29, U5.3, U5.4, U5.13, U6.2, U7.3, U8.2, Z1.1
unnamed: C1.1, U2.2, X1.1
unnamed: C4.1, R3.1, X1.3
unnamed: C7.1, FB2.2, U3.1
unnamed: C10.1, R14.1, X2.1
unnamed: C12.1, U4.13, X2.3
unnamed: C18.1, C23.1, FB3.1, U6.6, U7.5
unnamed: C22.1, J3.2, R1.1, U8.6
unnamed: C30.1, FB5.1, L1.2, R25.1, U5.5
unnamed: C33.1, FB3.2, J3.1, U8.5
unnamed: C37.1, Z1.3
unnamed: J1.4, R4.1
unnamed: J1.6, R5.1
unnamed: L1.1, U5.2
unnamed: L2.1, L3.1
unnamed: L2.3, U4.19
unnamed: L2.4, U4.17
unnamed: L3.2, Z1.2
unnamed: R1.2, U7.4
unnamed: R2.1, U2.31
unnamed: R3.2, U2.3
unnamed: R14.2, U4.12
unnamed: R15.2, U3.4, U5.12
unnamed: R20.1, U6.5
P3V3: C2.1, C3.1, C5.1, C6.1, C14.1, C15.1, C16.1, C17.1, C19.1, C20.1, C21.1, FB5.2, J1.2, R19.1, U2.1, U2.5, U2.17, U4.8, U4.11, U4.14, U4.16, U4.20, U4.22, U4.24
P5V0: C9.1, C11.1, C13.1, C24.1, R15.1, U3.5, U5.1, U5.8, U5.9, U5.10, U5.11, U6.1

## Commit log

2016-07-30 Removed junk files
2016-07-30 Added PDF schematic
2016-07-30 Added HTML BOM
2016-07-30 Added BOM and PDF schematic
2016-08-07 Added missing cache-file
2016-08-07 added 3d models
